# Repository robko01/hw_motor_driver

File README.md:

# hw_motor_driver
This repo is holding design files for the linear transporter and rotation table motor driver.

The board is designed in KiCAD.

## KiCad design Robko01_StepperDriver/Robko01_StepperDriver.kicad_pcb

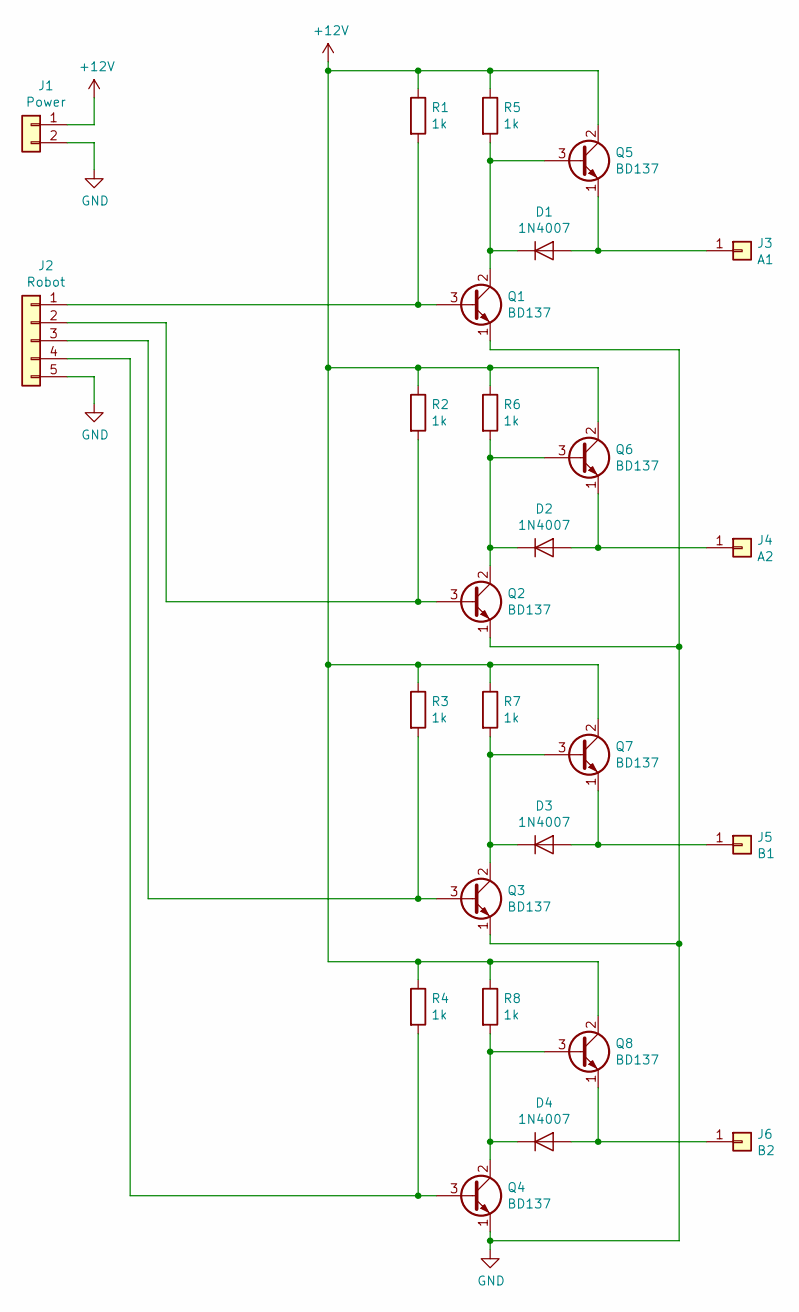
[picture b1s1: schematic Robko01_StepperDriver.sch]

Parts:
D1, D2, D3, D4: 1N4007; D_DO-41_SOD81_P5.08mm_Vertical_KathodeUp
J1: Power; PhoenixContact_MSTBVA_2,5_2-G-5,08_1x02_P5.08mm_Vertical
J2: Robot; PinHeader_1x05_P2.54mm_Vertical
J3: A1; PinHeader_1x01_P2.54mm_Vertical
J4: A2; PinHeader_1x01_P2.54mm_Vertical
J5: B1; PinHeader_1x01_P2.54mm_Vertical
J6: B2; PinHeader_1x01_P2.54mm_Vertical
Q1, Q2, Q3, Q4, Q5, Q6, Q7, Q8: BD137; TO-126-3_Vertical
R1, R2, R3, R4, R5, R6, R7, R8: 1k; R_Axial_DIN0207_L6.3mm_D2.5mm_P10.16mm_Horizontal

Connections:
+12V: J1.1, Q5.2 (C), Q6.2 (C), Q7.2 (C), Q8.2 (C), R1.1, R2.1, R3.1, R4.1, R5.1, R6.1, R7.1, R8.1
GND: J1.2, J2.5, Q1.1 (E), Q2.1 (E), Q3.1 (E), Q4.1 (E)
unnamed: D1.1 (K), Q1.2 (C), Q5.3 (B), R5.2
unnamed: D1.2 (A), J3.1, Q5.1 (E)
unnamed: D2.1 (K), Q2.2 (C), Q6.3 (B), R6.2
unnamed: D2.2 (A), J4.1, Q6.1 (E)
unnamed: D3.1 (K), Q3.2 (C), Q7.3 (B), R7.2
unnamed: D3.2 (A), J5.1, Q7.1 (E)
unnamed: D4.1 (K), Q4.2 (C), Q8.3 (B), R8.2
unnamed: D4.2 (A), J6.1, Q8.1 (E)
unnamed: J2.1, Q1.3 (B), R1.2
unnamed: J2.2, Q2.3 (B), R2.2
unnamed: J2.3, Q3.3 (B), R3.2
unnamed: J2.4, Q4.3 (B), R4.2

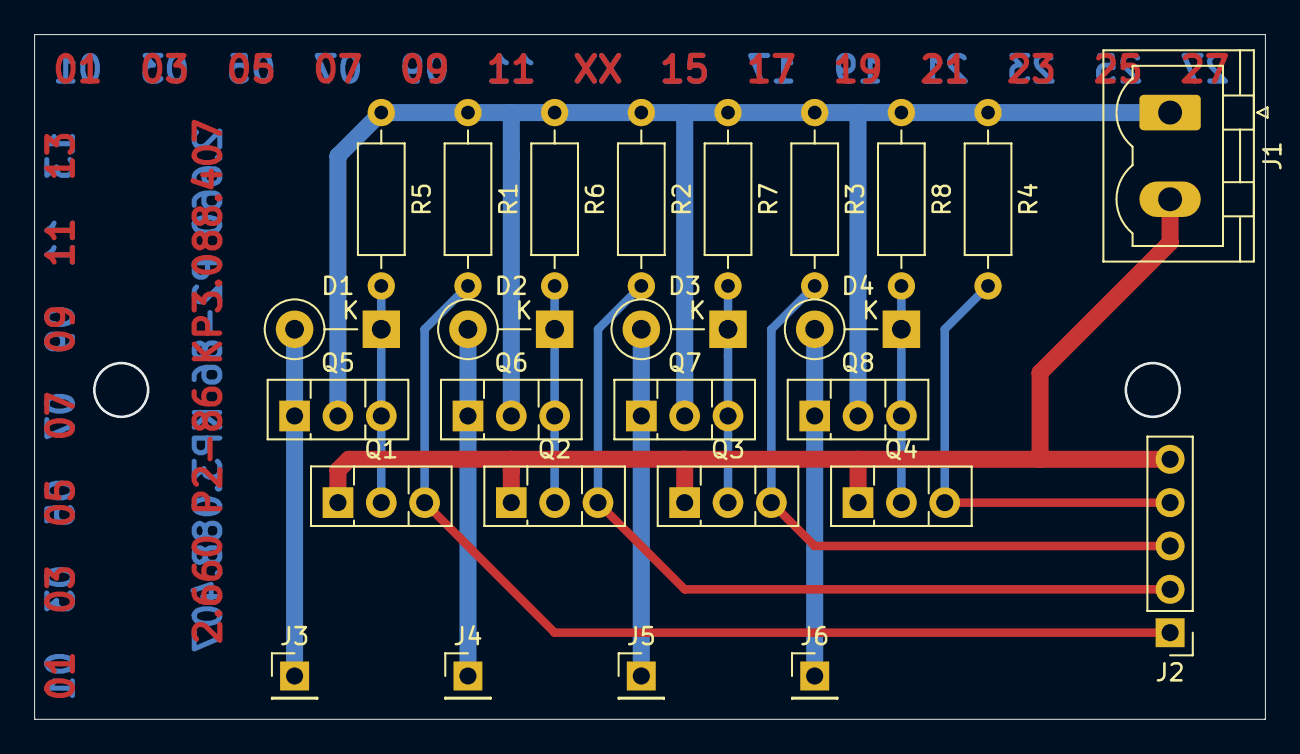
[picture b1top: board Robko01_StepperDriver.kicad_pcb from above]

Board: 2 copper layers, 72.1 x 40.1 mm, 26 parts (0 on the bottom side), 14 nets.

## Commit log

2020-08-17 Add design files
2020-08-30 Add ignore file
